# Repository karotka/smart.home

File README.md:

**Setup & architecture:** see [`CLAUDE.md`](CLAUDE.md) for the full orientation map
(hosts, services, deploy, data plane) and [`servers.conf/README.md`](servers.conf/README.md)
for the nginx / Cloudflare-tunnel / TLS proxy layer.

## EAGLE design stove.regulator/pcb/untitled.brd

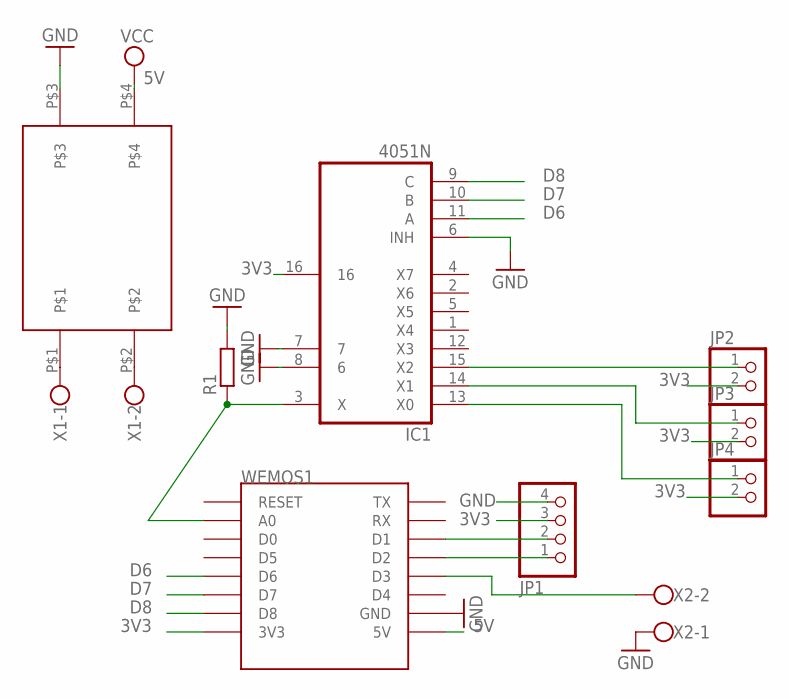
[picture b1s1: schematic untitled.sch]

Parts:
IC1: 4051N; DIL16
JP1: PINHD-1X4; 1X04
JP2, JP3, JP4: PINHD-1X2; 1X02
R1: R-EU_0207/10; 0207/10
U$6: HLK-PM01
WEMOS1: WEMOS-D1-MINI
X1, X2: W237-102

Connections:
3V3: IC1.16, JP1.3, JP2.2, JP3.2, JP4.2, WEMOS1.3V3
5V: U$6.P$4, WEMOS1.5V
D6: IC1.11 (A), WEMOS1.D6
D7: IC1.10 (B), WEMOS1.D7
D8: IC1.9 (C), WEMOS1.D8
GND: IC1.6 (INH), IC1.7, IC1.8 (6), JP1.4, R1.2, U$6.P$3, WEMOS1.GND, X2.1
unnamed: IC1.3 (X), R1.1, WEMOS1.A0
unnamed: IC1.13 (X0), JP4.1
unnamed: IC1.14 (X1), JP3.1
unnamed: IC1.15 (X2), JP2.1
unnamed: JP1.1, WEMOS1.D2
unnamed: JP1.2, WEMOS1.D1
unnamed: U$6.P$1, X1.1
unnamed: U$6.P$2, X1.2
unnamed: WEMOS1.D3, X2.2

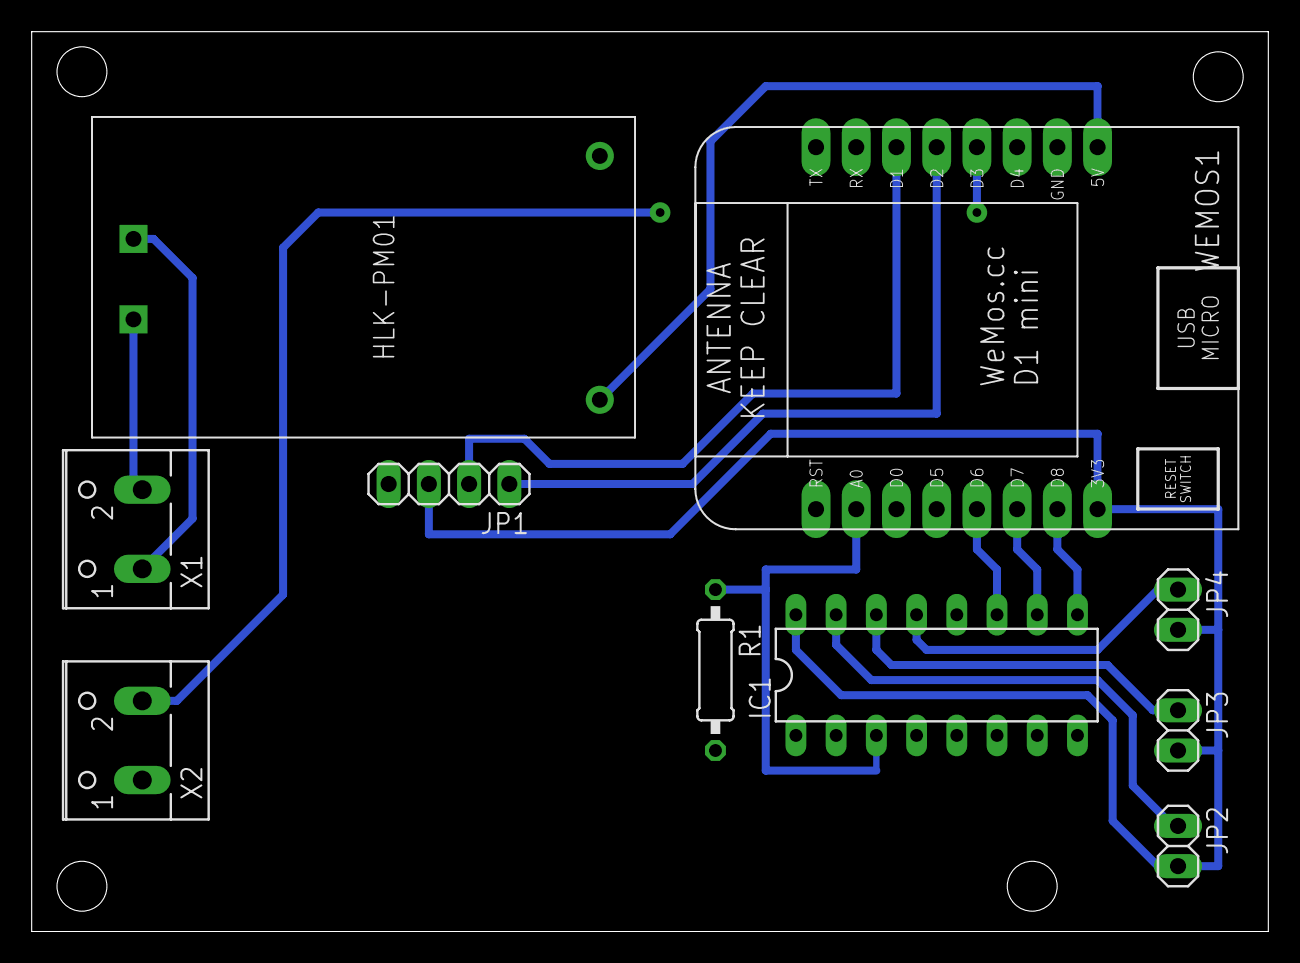
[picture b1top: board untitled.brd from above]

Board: 2 copper layers, 78.1 x 56.8 mm, 10 parts (0 on the bottom side), 15 nets.

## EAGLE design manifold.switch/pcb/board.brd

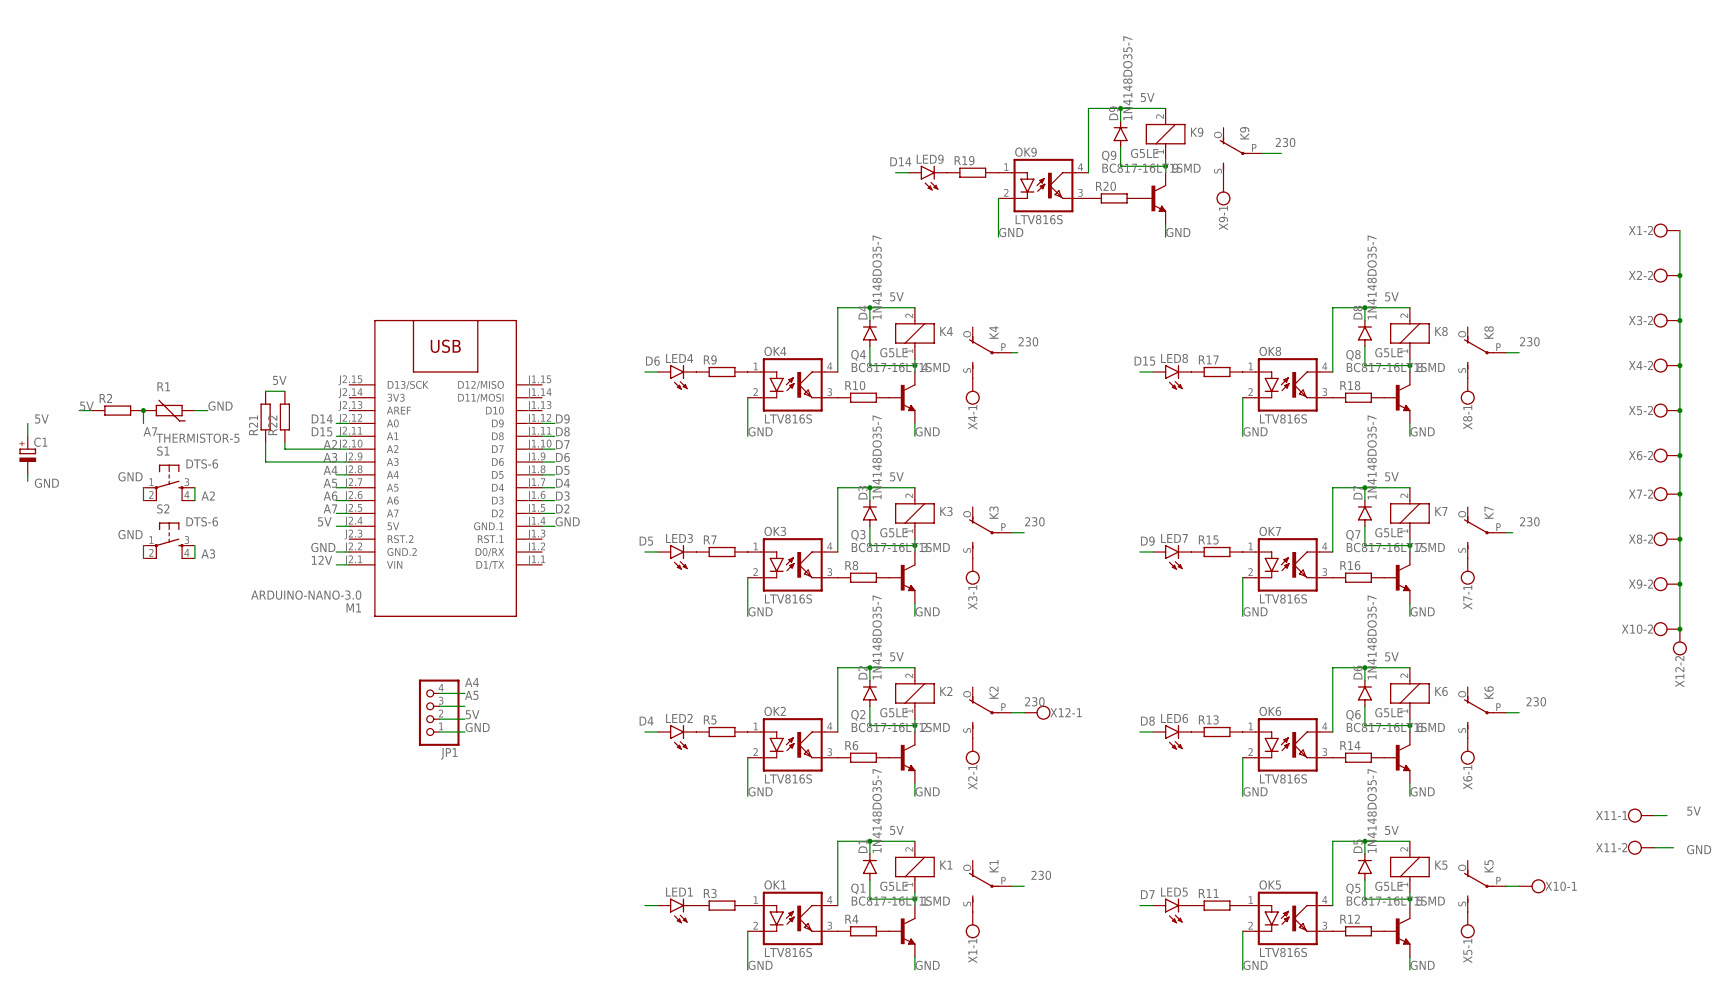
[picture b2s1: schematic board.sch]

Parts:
C1: CPOL-EUB45181A; B45181A
D1, D2, D3, D4, D5, D6, D7, D8, D9: 1N4148DO35-7; DO35-7
JP1: PINHD-1X4; 1X04
K1, K2, K3, K4, K5, K6, K7, K8, K9: G5LE
LED1, LED2, LED3, LED4, LED5, LED6, LED7, LED8, LED9: LED3MM
M1: ARDUINO-NANO-3.0
OK1, OK2, OK3, OK4, OK5, OK6, OK7, OK8, OK9: LTV816S; DIL4-SMD
Q1, Q2, Q3, Q4, Q5, Q6, Q7, Q8, Q9: BC817-16LT1SMD; SOT23-BEC
R1: THERMISTOR-5; R-5
R2, R21, R22: R-EU_0207/10; 0207/10
R3, R4, R5, R6, R7, R8, R9, R10, R11, R12, R13, R14, R15, R16, R17, R18, R19, R20: R-EU_R1206; R1206
S1, S2: DTS-6
X1, X2, X3, X4, X5, X6, X7, X8, X9, X10, X11, X12: W237-102

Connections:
1: D1.A, K1.1, Q1.C
2: D2.A, K2.1, Q2.C
3: D3.A, K3.1, Q3.C
3V3: M1.J2.14 (3V3)
4: D4.A, K4.1, Q4.C
5: D5.A, K5.1, Q5.C
5V: C1.+, D1.C, D2.C, D3.C, D4.C, D5.C, D6.C, D7.C, D8.C, D9.C, JP1.2, K1.2, K2.2, K3.2, K4.2, K5.2, K6.2, K7.2, K8.2, K9.2, M1.J2.4 (5V), OK1.4 (COL), OK2.4 (COL), OK3.4 (COL), OK4.4 (COL), OK5.4 (COL), OK6.4 (COL), OK7.4 (COL), OK8.4 (COL), OK9.4 (COL), R2.1, R21.2, R22.2, X11.1
6: D6.A, K6.1, Q6.C
7: D7.A, K7.1, Q7.C
8: D8.A, K8.1, Q8.C
9: D9.A, K9.1, Q9.C
12V: M1.J2.1 (VIN)
230: K1.P, K2.P, K3.P, K4.P, K5.P, K6.P, K7.P, K8.P, K9.P, X10.1, X12.1
A2: M1.J2.10 (A2), R22.1, S1.3, S1.4
A3: M1.J2.9 (A3), R21.1, S2.3, S2.4
A4: JP1.4, M1.J2.8 (A4)
A5: JP1.3, M1.J2.7 (A5)
A6: M1.J2.6 (A6)
A7: M1.J2.5 (A7), R1.2, R2.2
D2: M1.J1.5 (D2)
D3: LED1.A, M1.J1.6 (D3)
D4: LED2.A, M1.J1.7 (D4)
D5: LED3.A, M1.J1.8 (D5)
D6: LED4.A, M1.J1.9 (D6)
D7: LED5.A, M1.J1.10 (D7)
D8: LED6.A, M1.J1.11 (D8)
D9: LED7.A, M1.J1.12 (D9)
D14: LED9.A, M1.J2.12 (A0)
D15: LED8.A, M1.J2.11 (A1)
GND: C1.-, JP1.1, M1.J1.4 (GND.1), M1.J2.2 (GND.2), OK1.2 (C), OK2.2 (C), OK3.2 (C), OK4.2 (C), OK5.2 (C), OK6.2 (C), OK7.2 (C), OK8.2 (C), OK9.2 (C), Q1.E, Q2.E, Q3.E, Q4.E, Q5.E, Q6.E, Q7.E, Q8.E, Q9.E, R1.1, S1.1, S1.2, S2.1, S2.2, X11.2
unnamed: OK1.1 (A), R3.2
unnamed: LED1.K (C), R3.1
unnamed: OK1.3 (EMIT), R4.1
unnamed: Q1.B, R4.2
unnamed: K1.S, X1.1
unnamed: OK2.1 (A), R5.2
unnamed: LED2.K (C), R5.1
unnamed: OK2.3 (EMIT), R6.1
unnamed: Q2.B, R6.2
unnamed: K2.S, X2.1
unnamed: K3.S, X3.1
unnamed: OK3.1 (A), R7.2
unnamed: LED3.K (C), R7.1
unnamed: OK3.3 (EMIT), R8.1
unnamed: Q3.B, R8.2
unnamed: K4.S, X4.1
unnamed: OK4.1 (A), R9.2
unnamed: LED4.K (C), R9.1
unnamed: OK4.3 (EMIT), R10.1
unnamed: Q4.B, R10.2
unnamed: K5.S, X5.1
unnamed: OK5.1 (A), R11.2
unnamed: LED5.K (C), R11.1
unnamed: OK5.3 (EMIT), R12.1
unnamed: Q5.B, R12.2
unnamed: K6.S, X6.1
unnamed: OK6.1 (A), R13.2
unnamed: LED6.K (C), R13.1
unnamed: OK6.3 (EMIT), R14.1
unnamed: Q6.B, R14.2
unnamed: K7.S, X7.1
unnamed: OK7.1 (A), R15.2
unnamed: LED7.K (C), R15.1
unnamed: OK7.3 (EMIT), R16.1
unnamed: Q7.B, R16.2
unnamed: K8.S, X8.1
unnamed: OK8.1 (A), R17.2
unnamed: LED8.K (C), R17.1
unnamed: OK8.3 (EMIT), R18.1
unnamed: Q8.B, R18.2
unnamed: K9.S, X9.1
unnamed: OK9.1 (A), R19.2
unnamed: LED9.K (C), R19.1
unnamed: OK9.3 (EMIT), R20.1
unnamed: Q9.B, R20.2
unnamed: X1.2, X2.2, X3.2, X4.2, X5.2, X6.2, X7.2, X8.2, X9.2, X10.2, X12.2

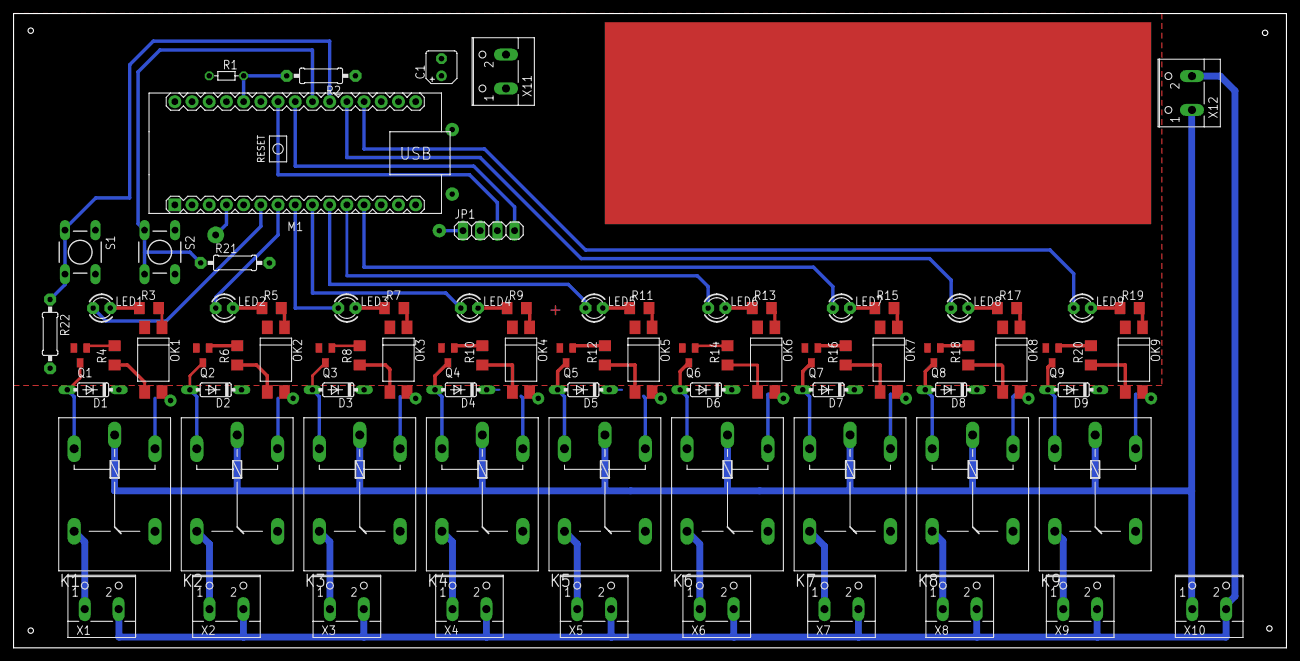
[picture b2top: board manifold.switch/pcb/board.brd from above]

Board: 2 copper layers, 187.9 x 93.7 mm, 84 parts (0 on the bottom side), 72 nets.

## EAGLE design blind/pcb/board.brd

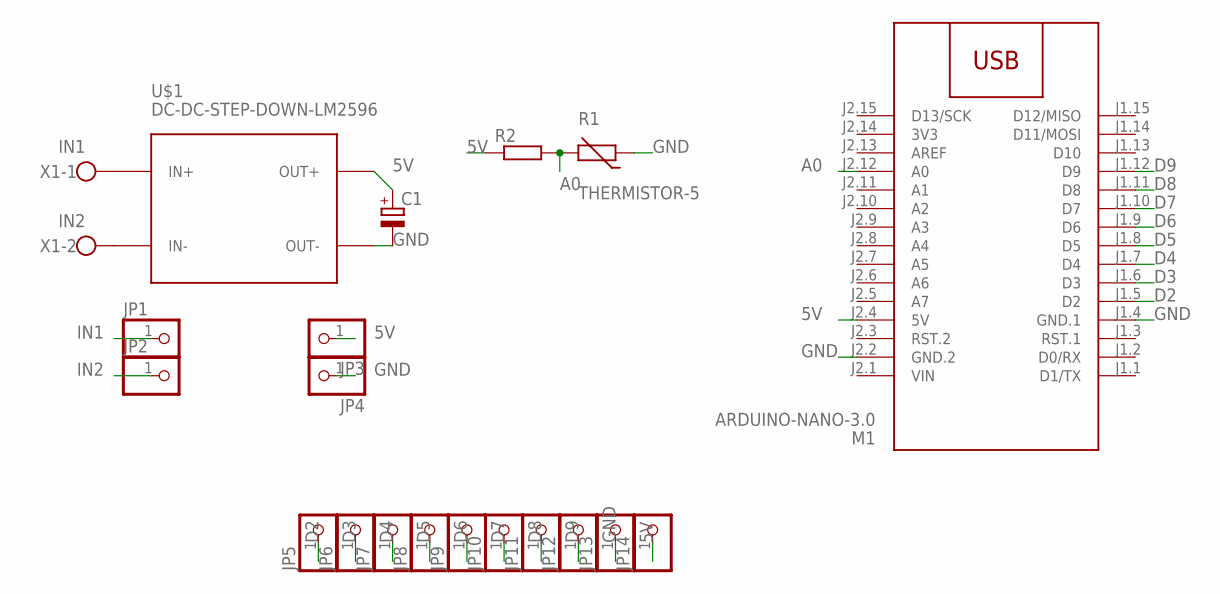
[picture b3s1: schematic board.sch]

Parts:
C1: CPOL-EUB45181A; B45181A
JP1, JP2, JP3, JP4, JP5, JP6, JP7, JP8, JP9, JP10, JP11, JP12, JP13, JP14: PINHD-1X1; 1X01
M1: ARDUINO-NANO-3.0
R1: THERMISTOR-5; R-5
R2: R-EU_0207/10; 0207/10
U$1: DC-DC-STEP-DOWN-LM2596
X1: W237-102

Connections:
3V3: M1.J2.14 (3V3)
5V: C1.+, JP3.1, JP14.1, M1.J2.4 (5V), R2.1, U$1.OUT+
A0: M1.J2.12 (A0), R1.2, R2.2
D2: JP5.1, M1.J1.5 (D2)
D3: JP6.1, M1.J1.6 (D3)
D4: JP7.1, M1.J1.7 (D4)
D5: JP8.1, M1.J1.8 (D5)
D6: JP9.1, M1.J1.9 (D6)
D7: JP10.1, M1.J1.10 (D7)
D8: JP11.1, M1.J1.11 (D8)
D9: JP12.1, M1.J1.12 (D9)
GND: C1.-, JP4.1, JP13.1, M1.J1.4 (GND.1), M1.J2.2 (GND.2), R1.1, U$1.OUT-
IN1: JP1.1, U$1.IN+, X1.1
IN2: JP2.1, U$1.IN-, X1.2
VIN: M1.J2.1 (VIN)

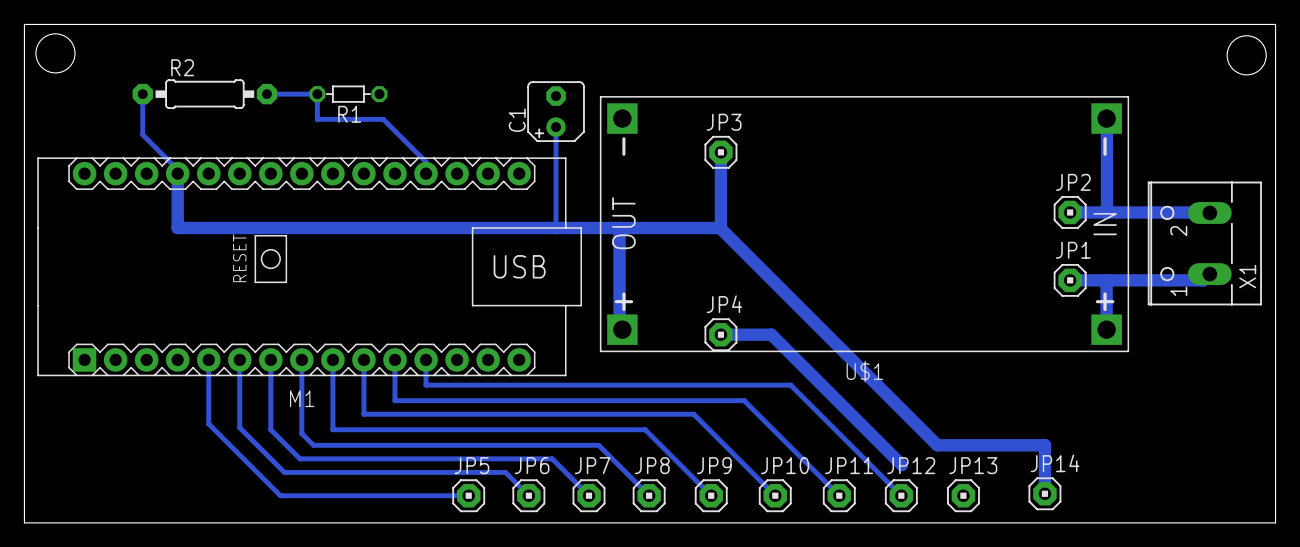
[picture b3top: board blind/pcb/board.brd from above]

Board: 2 copper layers, 102.4 x 40.8 mm, 20 parts (0 on the bottom side), 13 nets.

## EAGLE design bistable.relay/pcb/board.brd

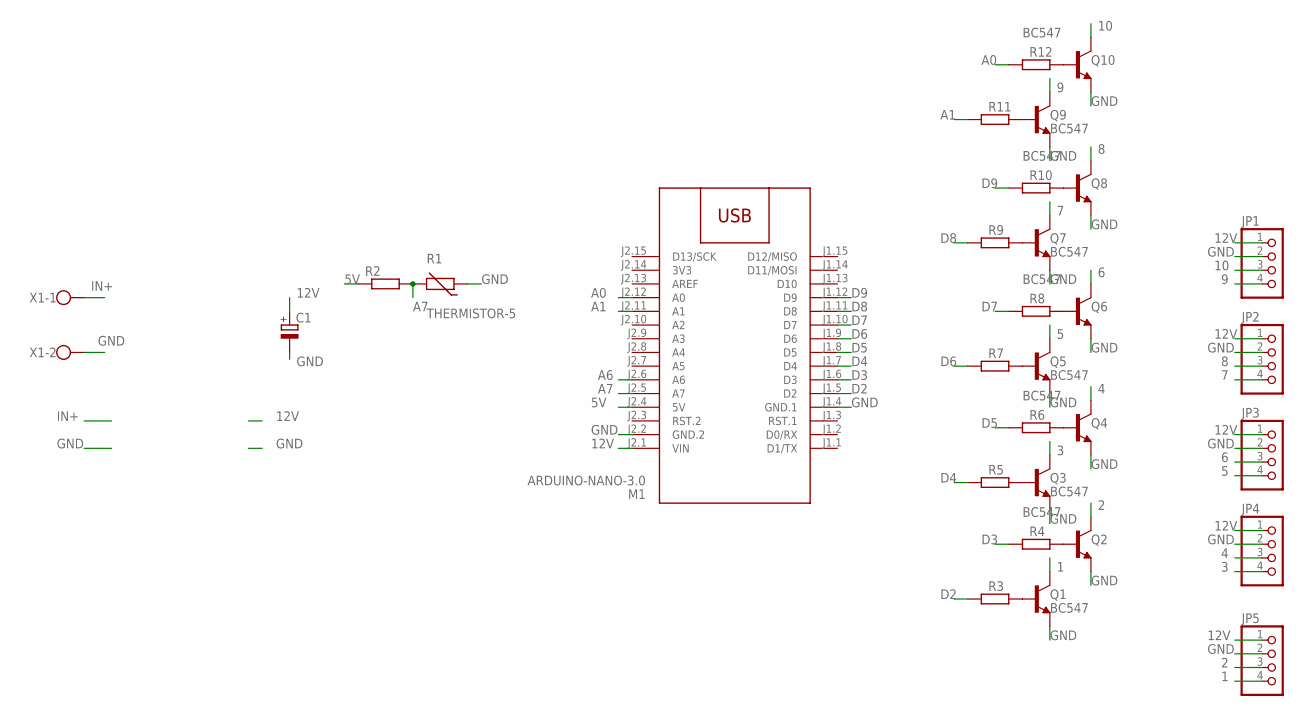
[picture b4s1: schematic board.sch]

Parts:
C1: CPOL-EUB45181A; B45181A
JP1, JP2, JP3, JP4, JP5: PINHD-1X4; 1X04
M1: ARDUINO-NANO-3.0
Q1, Q2, Q3, Q4, Q5, Q6, Q7, Q8, Q9, Q10: BC547; TO92
R1: THERMISTOR-5; R-5
R2, R3, R4, R5, R6, R7, R8, R9, R10, R11, R12: R-EU_0207/10; 0207/10
X1: W237-102

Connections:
1: JP5.4, Q1.3 (C)
2: JP5.3, Q2.3 (C)
3: JP4.4, Q3.3 (C)
3V3: M1.J2.14 (3V3)
4: JP4.3, Q4.3 (C)
5: JP3.4, Q5.3 (C)
5V: M1.J2.4 (5V), R2.1
6: JP3.3, Q6.3 (C)
7: JP2.4, Q7.3 (C)
8: JP2.3, Q8.3 (C)
9: JP1.4, Q9.3 (C)
10: JP1.3, Q10.3 (C)
12V: C1.+, JP1.1, JP2.1, JP3.1, JP4.1, JP5.1, M1.J2.1 (VIN)
A0: M1.J2.12 (A0), R12.1
A1: M1.J2.11 (A1), R11.1
A6: M1.J2.6 (A6)
A7: M1.J2.5 (A7), R1.2, R2.2
D2: M1.J1.5 (D2), R3.1
D3: M1.J1.6 (D3), R4.1
D4: M1.J1.7 (D4), R5.1
D5: M1.J1.8 (D5), R6.1
D6: M1.J1.9 (D6), R7.1
D7: M1.J1.10 (D7), R8.1
D8: M1.J1.11 (D8), R9.1
D9: M1.J1.12 (D9), R10.1
GND: C1.-, JP1.2, JP2.2, JP3.2, JP4.2, JP5.2, M1.J1.4 (GND.1), M1.J2.2 (GND.2), Q1.1 (E), Q2.1 (E), Q3.1 (E), Q4.1 (E), Q5.1 (E), Q6.1 (E), Q7.1 (E), Q8.1 (E), Q9.1 (E), Q10.1 (E), R1.1, X1.2
IN+: X1.1
unnamed: Q1.2 (B), R3.2
unnamed: Q2.2 (B), R4.2
unnamed: Q3.2 (B), R5.2
unnamed: Q4.2 (B), R6.2
unnamed: Q5.2 (B), R7.2
unnamed: Q6.2 (B), R8.2
unnamed: Q7.2 (B), R9.2
unnamed: Q8.2 (B), R10.2
unnamed: Q9.2 (B), R11.2
unnamed: Q10.2 (B), R12.2

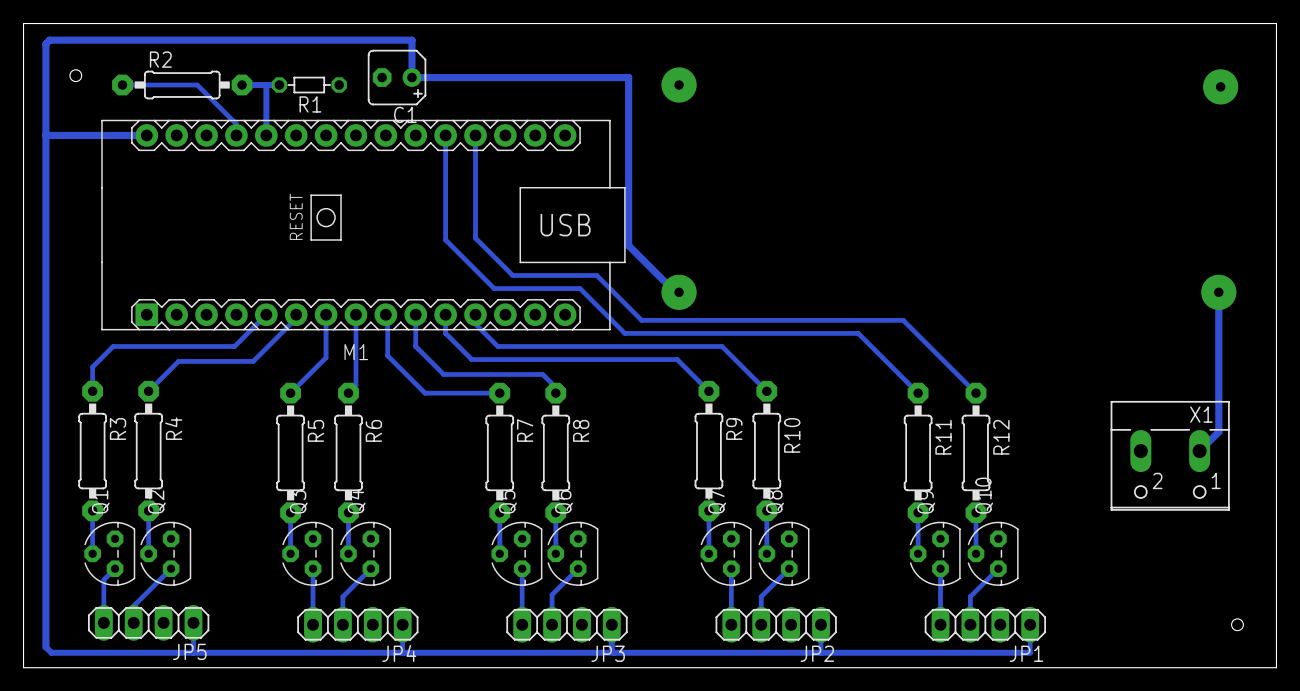
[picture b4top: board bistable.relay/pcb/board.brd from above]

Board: 2 copper layers, 106.5 x 54.8 mm, 30 parts (0 on the bottom side), 34 nets.

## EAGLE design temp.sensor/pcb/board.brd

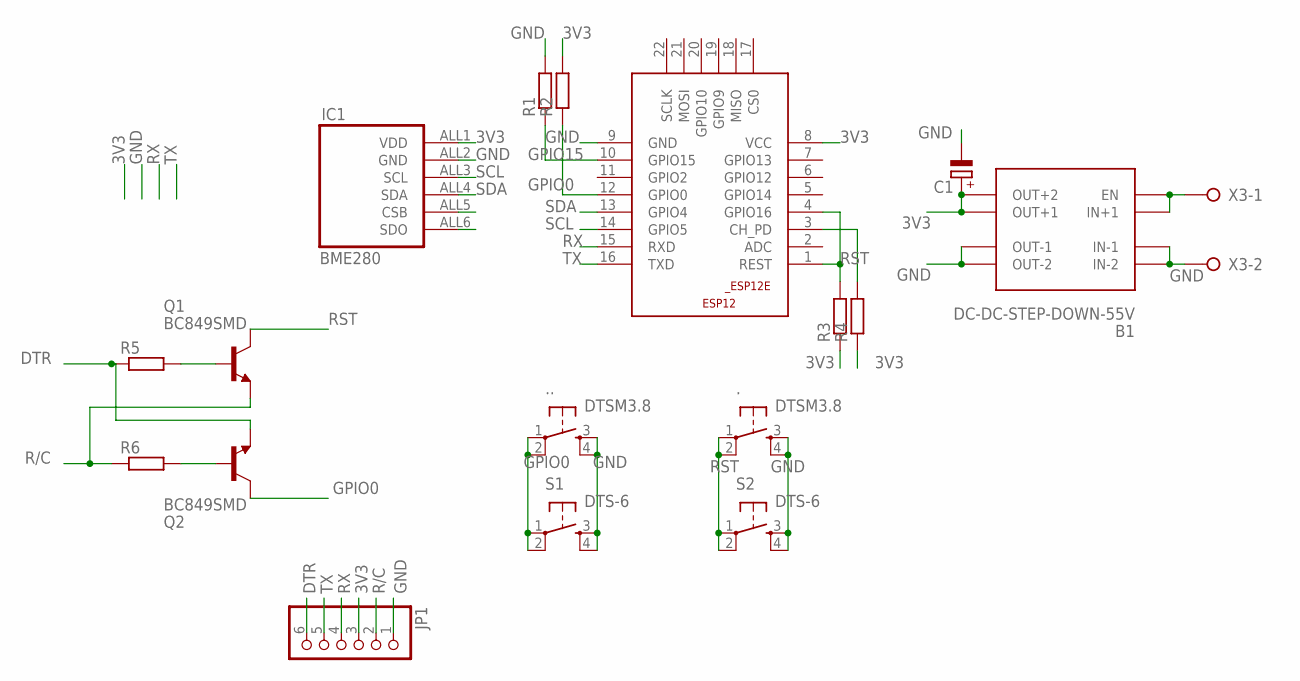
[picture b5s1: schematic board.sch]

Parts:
., ..: DTSM3.8
B1: DC-DC-STEP-DOWN-55V
C1: CPOL-EUE1.8-4; E1,8-4
ESP12: ESP8266-12EESP12E; ESP8266-ESP12E
IC1: BME280
JP1: PINHD-1X6/90; 1X06/90
Q1, Q2: BC849SMD; SOT23-BEC
R1, R2, R5, R6: R-EU_R1206; R1206
R3, R4: R-EU_0207/10; 0207/10
S1, S2: DTS-6
X3: W237-02P; W237-132

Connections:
3V3: B1.VOUT+1 (OUT+1), B1.VOUT+2 (OUT+2), C1.+, ESP12.8 (VCC), IC1.ALL1 (VDD), JP1.3, R2.2, R3.1, R4.1
DTR: JP1.6, Q2.E, R5.1
GND: ..3, ..4, ...3, ...4, B1.VIN-1 (IN-1), B1.VIN-2 (IN-2), B1.VOUT-1 (OUT-1), B1.VOUT-2 (OUT-2), C1.-, ESP12.9 (GND), IC1.ALL2 (GND), JP1.1, R1.2, S1.3, S1.4, S2.3, S2.4, X3.2
GPIO0: ...1, ...2, ESP12.12 (GPIO0), Q2.C, R2.1, S1.1, S1.2
GPIO15: ESP12.10 (GPIO15), R1.1
unnamed: ESP12.3 (CH_PD), R4.2
unnamed: B1.EN, B1.VIN+ (IN+1), X3.1
unnamed: Q1.B, R5.2
unnamed: Q2.B, R6.2
R/C: JP1.2, Q1.E, R6.1
RST: ..1, ..2, ESP12.1 (REST), ESP12.4 (GPIO16), Q1.C, R3.2, S2.1, S2.2
RX: ESP12.15 (RXD), JP1.4
SCL: ESP12.14 (GPIO5), IC1.ALL3 (SCL)
SDA: ESP12.13 (GPIO4), IC1.ALL4 (SDA)
TX: ESP12.16 (TXD), JP1.5

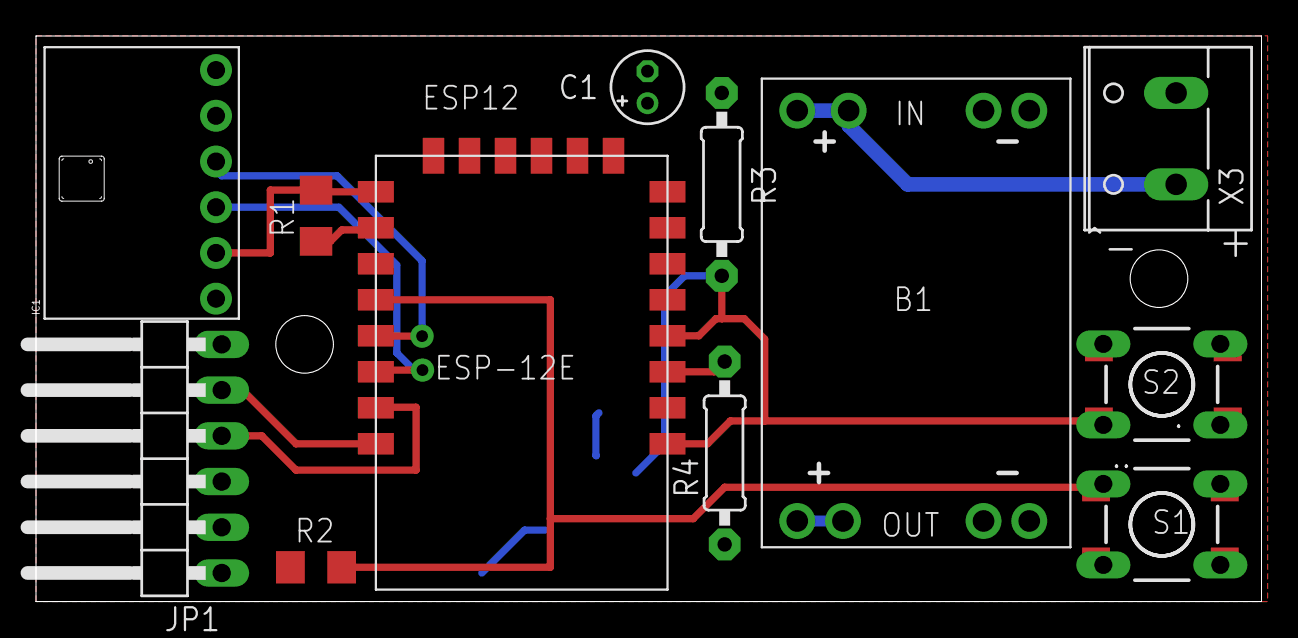
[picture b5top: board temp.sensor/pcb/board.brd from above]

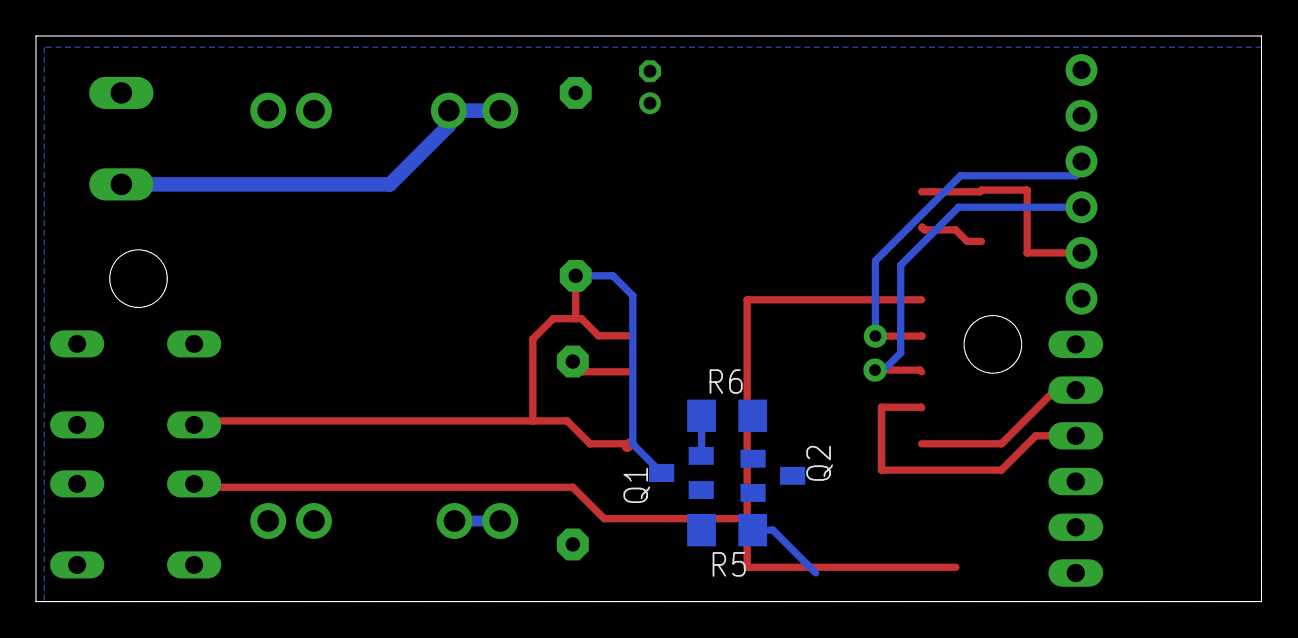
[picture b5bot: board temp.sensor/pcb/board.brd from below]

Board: 2 copper layers, 68.1 x 31.4 mm, 18 parts (4 on the bottom side), 15 nets.

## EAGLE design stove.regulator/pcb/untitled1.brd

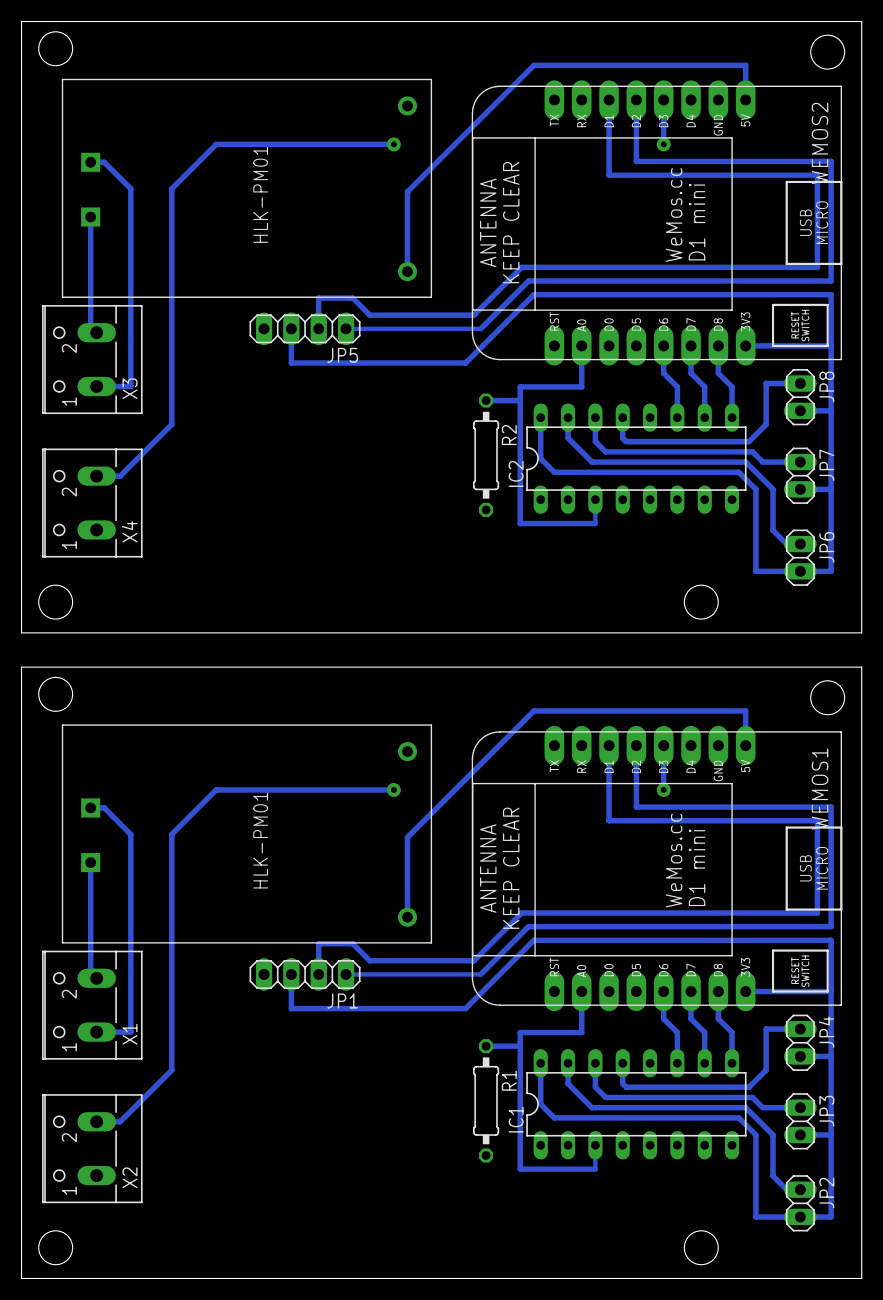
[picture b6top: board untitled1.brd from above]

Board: 2 copper layers, 78.1 x 116.8 mm, 20 parts (0 on the bottom side), 30 nets.

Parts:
IC1, IC2: 4051N; DIL16
JP1, JP5: 1X04
JP2, JP3, JP4, JP6, JP7, JP8: 1X02
R1, R2: 0207/10
U$1, U$6: HLK-PM01
WEMOS1, WEMOS2: WEMOS-D1-MINI
X1, X2, X3, X4: W237-102

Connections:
3V1: IC2.16, JP5.3, JP6.2, JP7.2, JP8.2, WEMOS2.3V3
3V3: IC1.16, JP1.3, JP2.2, JP3.2, JP4.2, WEMOS1.3V3
5V: U$6.P$4, WEMOS1.5V
5V1: U$1.P$4, WEMOS2.5V
D1: IC2.9, WEMOS2.D8
D2: IC2.10, WEMOS2.D7
D3: IC2.11, WEMOS2.D6
D6: IC1.11, WEMOS1.D6
D7: IC1.10, WEMOS1.D7
D8: IC1.9, WEMOS1.D8
GND: IC1.6, IC1.7, IC1.8, JP1.4, R1.2, U$6.P$3, X2.1
GND1: IC2.6, IC2.7, IC2.8, JP5.4, R2.2, U$1.P$3, X4.1
unnamed: IC1.3, R1.1, WEMOS1.A0
unnamed: IC1.13, JP4.1
unnamed: IC1.14, JP3.1
unnamed: IC1.15, JP2.1
unnamed: JP1.1, WEMOS1.D2
unnamed: JP1.2, WEMOS1.D1
unnamed: U$6.P$1, X1.1
unnamed: U$6.P$2, X1.2
unnamed: WEMOS1.D3, X2.2
unnamed: IC2.3, R2.1, WEMOS2.A0
unnamed: IC2.13, JP8.1
unnamed: IC2.14, JP7.1
unnamed: IC2.15, JP6.1
unnamed: JP5.1, WEMOS2.D2
unnamed: JP5.2, WEMOS2.D1
unnamed: U$1.P$1, X3.1
unnamed: U$1.P$2, X3.2
unnamed: WEMOS2.D3, X4.2

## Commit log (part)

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2026-06-14 smart-home: drop --rm so --restart=always doesn't conflict on newer dockerd
2026-06-14 smart-home: bind container to host port 8001 to match nginx upstream on .222
2026-06-23 config: rename rooms (Holky/Kluci/Ložnice) and replace the dead Petr sensor (10202255 → 10200555)
    Mirrors the live edits on .222. The new room labels match how the family
    actually refers to the bedrooms; the sensor swap retires the BME280 that
    was reading a stuck 50.6 °C (almost certainly water-loop temp because
    the probe was on a manifold port, not in the air).
2026-06-23 config: restore [Mqtt] section the scp from .222 wiped + deduplicate roomIds
    The previous commit copied web/conf/config.ini wholesale off .222, which
    doesn't have the [Mqtt] section the .224 container needs — gunicorn went
    into a restart loop on KeyError: 'Mqtt'. Restoring it on top of the room
    renames brings the container back.
    While here, kill the duplicated roomIds list — it lived in both [Heating]
    and [HeatingSensors] and would silently drift the moment one was renamed
2026-06-23 config: Redis lives on .224, not .222 — undo what the .222 scp dragged back in
2026-06-23 config: 10178502 moves from Obyvák to Skleník — testbed board redeployed to the greenhouse
2026-06-24 temp.sensor: longer WiFi timeout + log RSSI per publish
    60 s instead of 30 s — sklenik node was looping ESP.restart() because
    ESP8266 association sometimes takes 20-40 s in marginal RSSI spots, and
    the old 30 s timeout sent the chip back to setup() before the AP even
    answered. Wasted battery while never publishing.
    Every publish now carries the WiFi.RSSI() the chip actually saw in
    &s=<dBm>; /sensorTemp records it on the data dict and the boot line
2026-06-25 heat_pump: setpoint button follows the active work mode (heat vs cool)
    heatpump_chartLoad always handed the UI the heating PG1 setpoint, so in
    cool mode the button showed the heating target and the +/- pair edited
    the wrong DP. Now it picks PG1_COOLING_TARGET_TEMP when dps[5] == 'cool'
    and PG1_HEATING_TARGET_TEMP otherwise, caches both in Redis, and
    heatpump_setTemp routes the write to whichever setpoint matches the
    current mode.
2026-06-26 bms.monitor: move BMS_TX from D8/GPIO15 to D6/GPIO12 — strap-pin safe
    GPIO15 must be LOW at boot or the ESP8266 jumps into UART-download
    mode. The BMS RX line idles HIGH (3.3 V), so leaving the yellow wire
    on D8 would have held GPIO15 HIGH and made the module fail to boot
    from the DCE003 buck (USB flashing hid this with its DTR pulse).
    D6/GPIO12 has no strap-pin role and can be wired permanently.
2026-06-26 bms.monitor: ship a rolling 1 KB raw-byte capture in each POST when DEBUG_HEX_DUMP is on
    We need a way to reverse-engineer the temperature offsets without a
    serial cable — the BMS is already on battery power and the temperature
    the JK app reports (25.4 / 24.1 °C) doesn't match what the 0x82 0x20
    telemetry slots stream (constant 20.16). The real bytes must live in
    one of the bigger frames we haven't decoded yet.
    New jkRecentBytes() returns the last 1024 bytes of the UART stream as
2026-06-26 battery.html: cell bars use absolute Li-ion scale 3.0-4.2 V + mV labels under each bar
    Old per-pack min..max scaling made even a fully-charged pack look
    half-discharged because the lowest cell anchored the 20% baseline.
    Now every bar is scaled against a fixed 3.0 V (empty) - 4.2 V (full)
    Li-ion range so a full pack visually reads as ~full bars and the
    height across packs is directly comparable. Drift is communicated by
    two channels: the mV number printed under each bar, and red/blue
2026-06-26 battery.html: single-column layout under 1024 px so portrait tablets and phones get readable cards
    The auto-fill grid stayed on a 280 px minimum even on narrow screens,
    leaving one card with a big empty band beside it. Below 1024 px the
    grid collapses to one column at up to 720 px width, native scrolling
    replaces the in-card overflow trap (so iOS Safari scrolls cleanly),
    and the per-cell bars get a bit more height for legibility.
2026-06-26 battery card: min/avg/max in volts with unit at the end + bump mobile menu font
    Three values printed as 3-decimal volts (3.888 / 3.891 / 3.893 V) so the
    eye reads it as one block followed by a unit, instead of three bare mV
    counts. Delta stays in mV — it's the natural unit for cell drift.
    Mobile nav font 0.85rem -> 0.95rem with a small padding bump and matching
    body padding-bottom so the 6-item 3x2 grid still doesn't crowd the page
    content.
2026-06-26 bms.monitor: decode pack current from offset 2-3 of the 0x82 0x10 frame
    Pinned the field down with a known-state capture: user ran the pack
    at -6 A discharge, the raw stream showed bes16 at offset 2-3 = -63
    (= -6.3 A in 0.1 A units), and the |power| field at offset 40-41
    came out 3394 = 339 W, matching |6.3 × 54.4| within rounding.
    So:
    offset 2-3 signed int16 BE current in 0.1 A (× 100 -> mA)
2026-06-26 checker: terasa nightly close shifts from 22:00 to midnight
    User asked for the obyvak/terasa blind close to move to midnight.
    TERASA_CAL_HOUR 22 -> 0 makes the guard never true, so
    the routine arms as soon as the date rolls over and the 'ran today'
    flag in Redis is still yesterday's. First tick after 00:00 closes the
    cover; subsequent ticks return because last == today.
2026-06-27 heat_pump: cap the chart grid at 70vh / 720px so each chart is readable on a wide screen
    Full-viewport stretch on a 27" monitor was making each chart 470 px tall
    which felt empty — capped to 70vh (about 320 px per chart on 1080p)
    with a 1400 px max-width so a Cinema-display user doesn't get one
    continent-wide column either.

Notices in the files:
parts and their libraries:
diy-modules: Released under the Creative Commons Attribution 4.0 International License: http://creativecommons.org/licenses/by/4.0
